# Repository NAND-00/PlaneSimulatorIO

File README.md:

# PlaneSimulatorIO
Plug'n'play I/O board for connecting flight simulator controls to the PC/MAC via USB with extended X-Plane support.

The I/O board is a USB-HID device designed to connect your flight simulator controls to the flight simulator program. It supports up to 32 digital inputs (buttons or switches), two motorized trims with servo indicators, flaps lever with a servo indicator, fuel quadrant, yoke, pedals and a gear switch with three LED indicators.

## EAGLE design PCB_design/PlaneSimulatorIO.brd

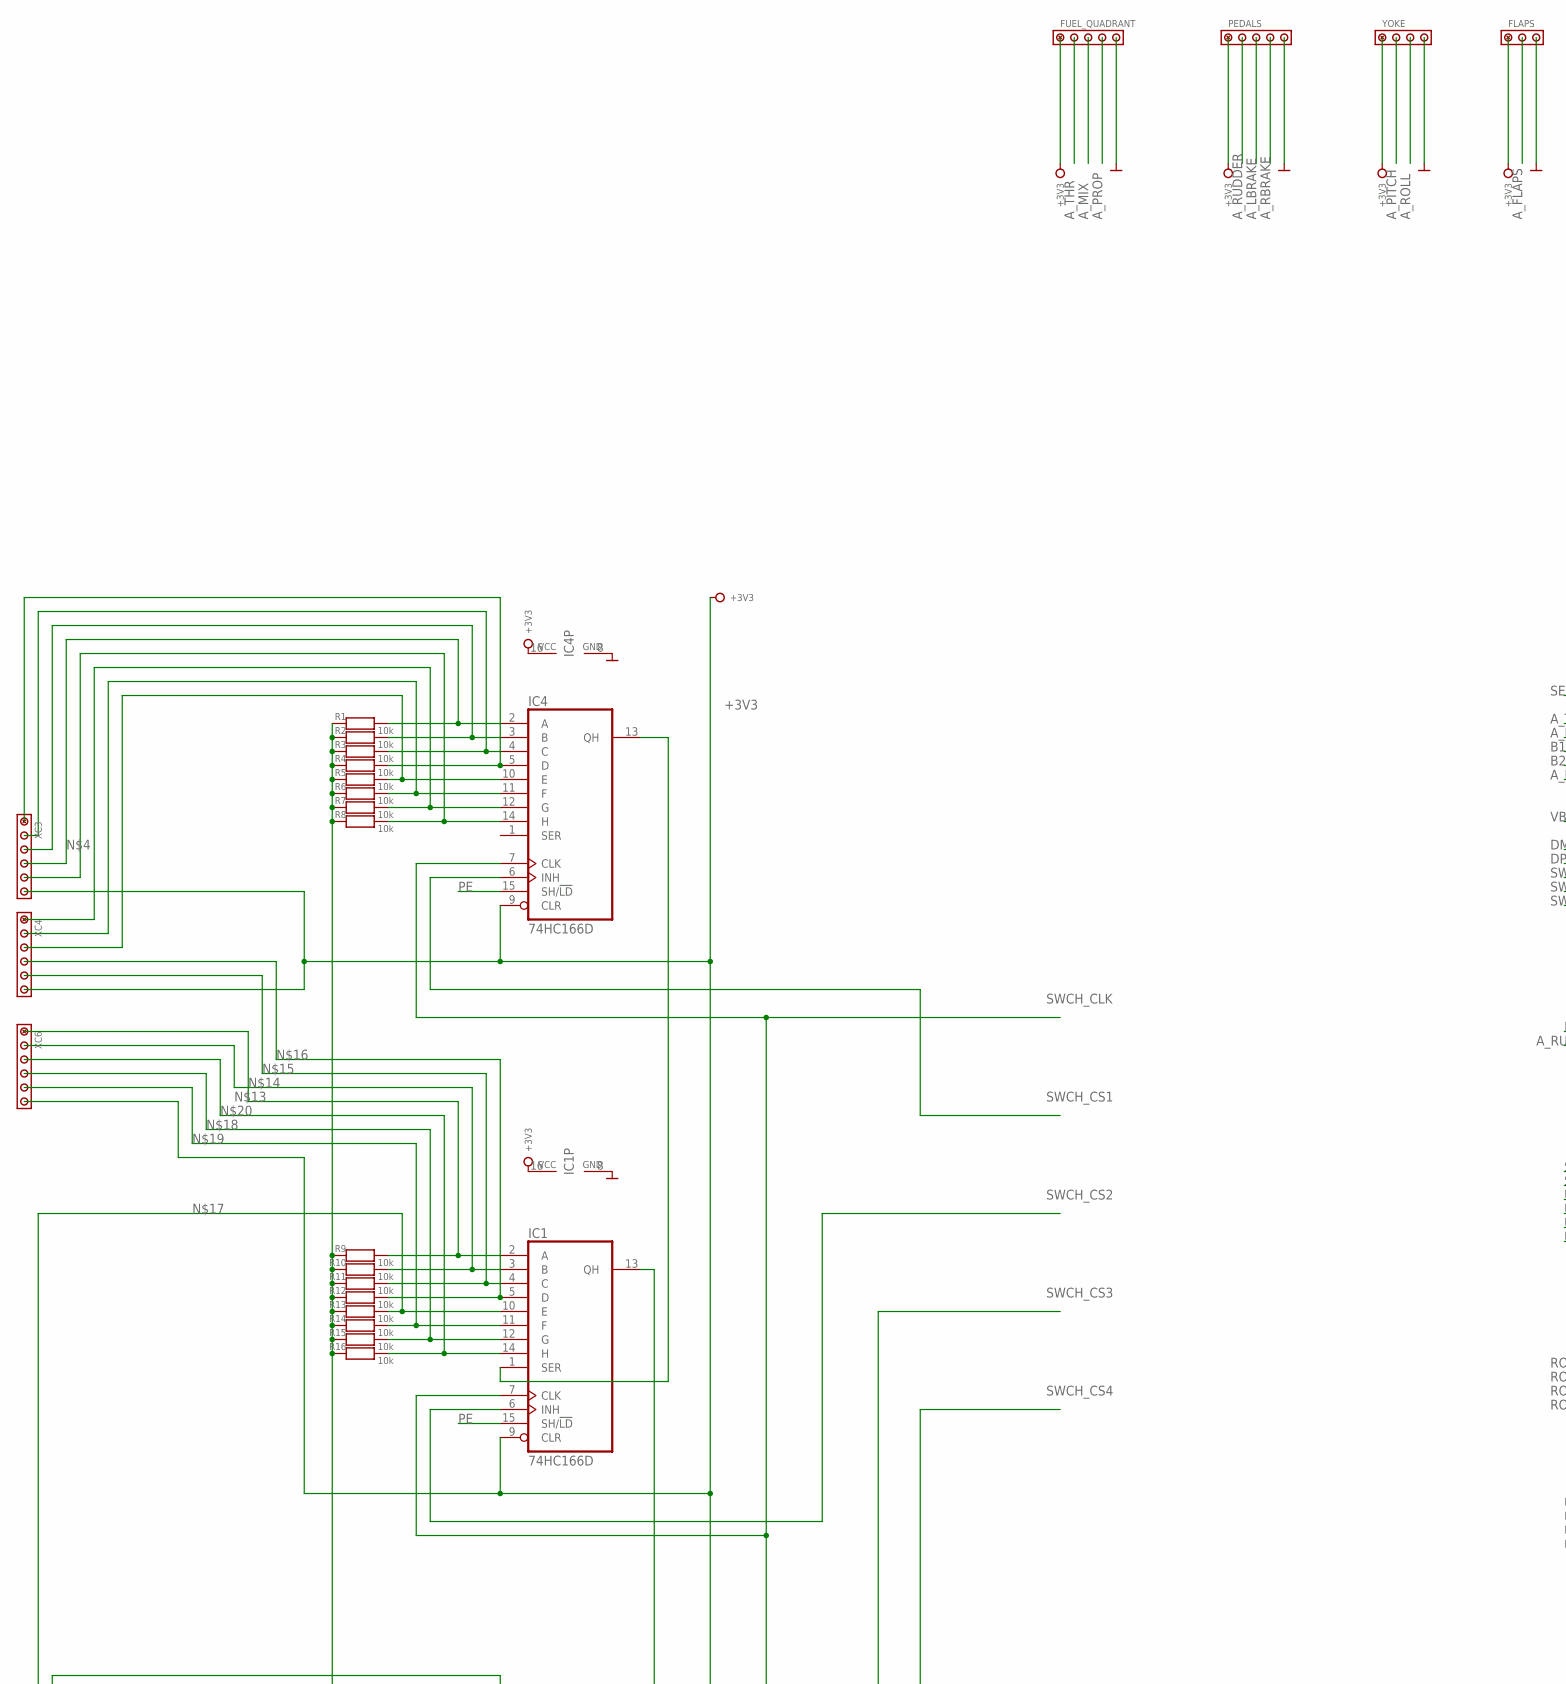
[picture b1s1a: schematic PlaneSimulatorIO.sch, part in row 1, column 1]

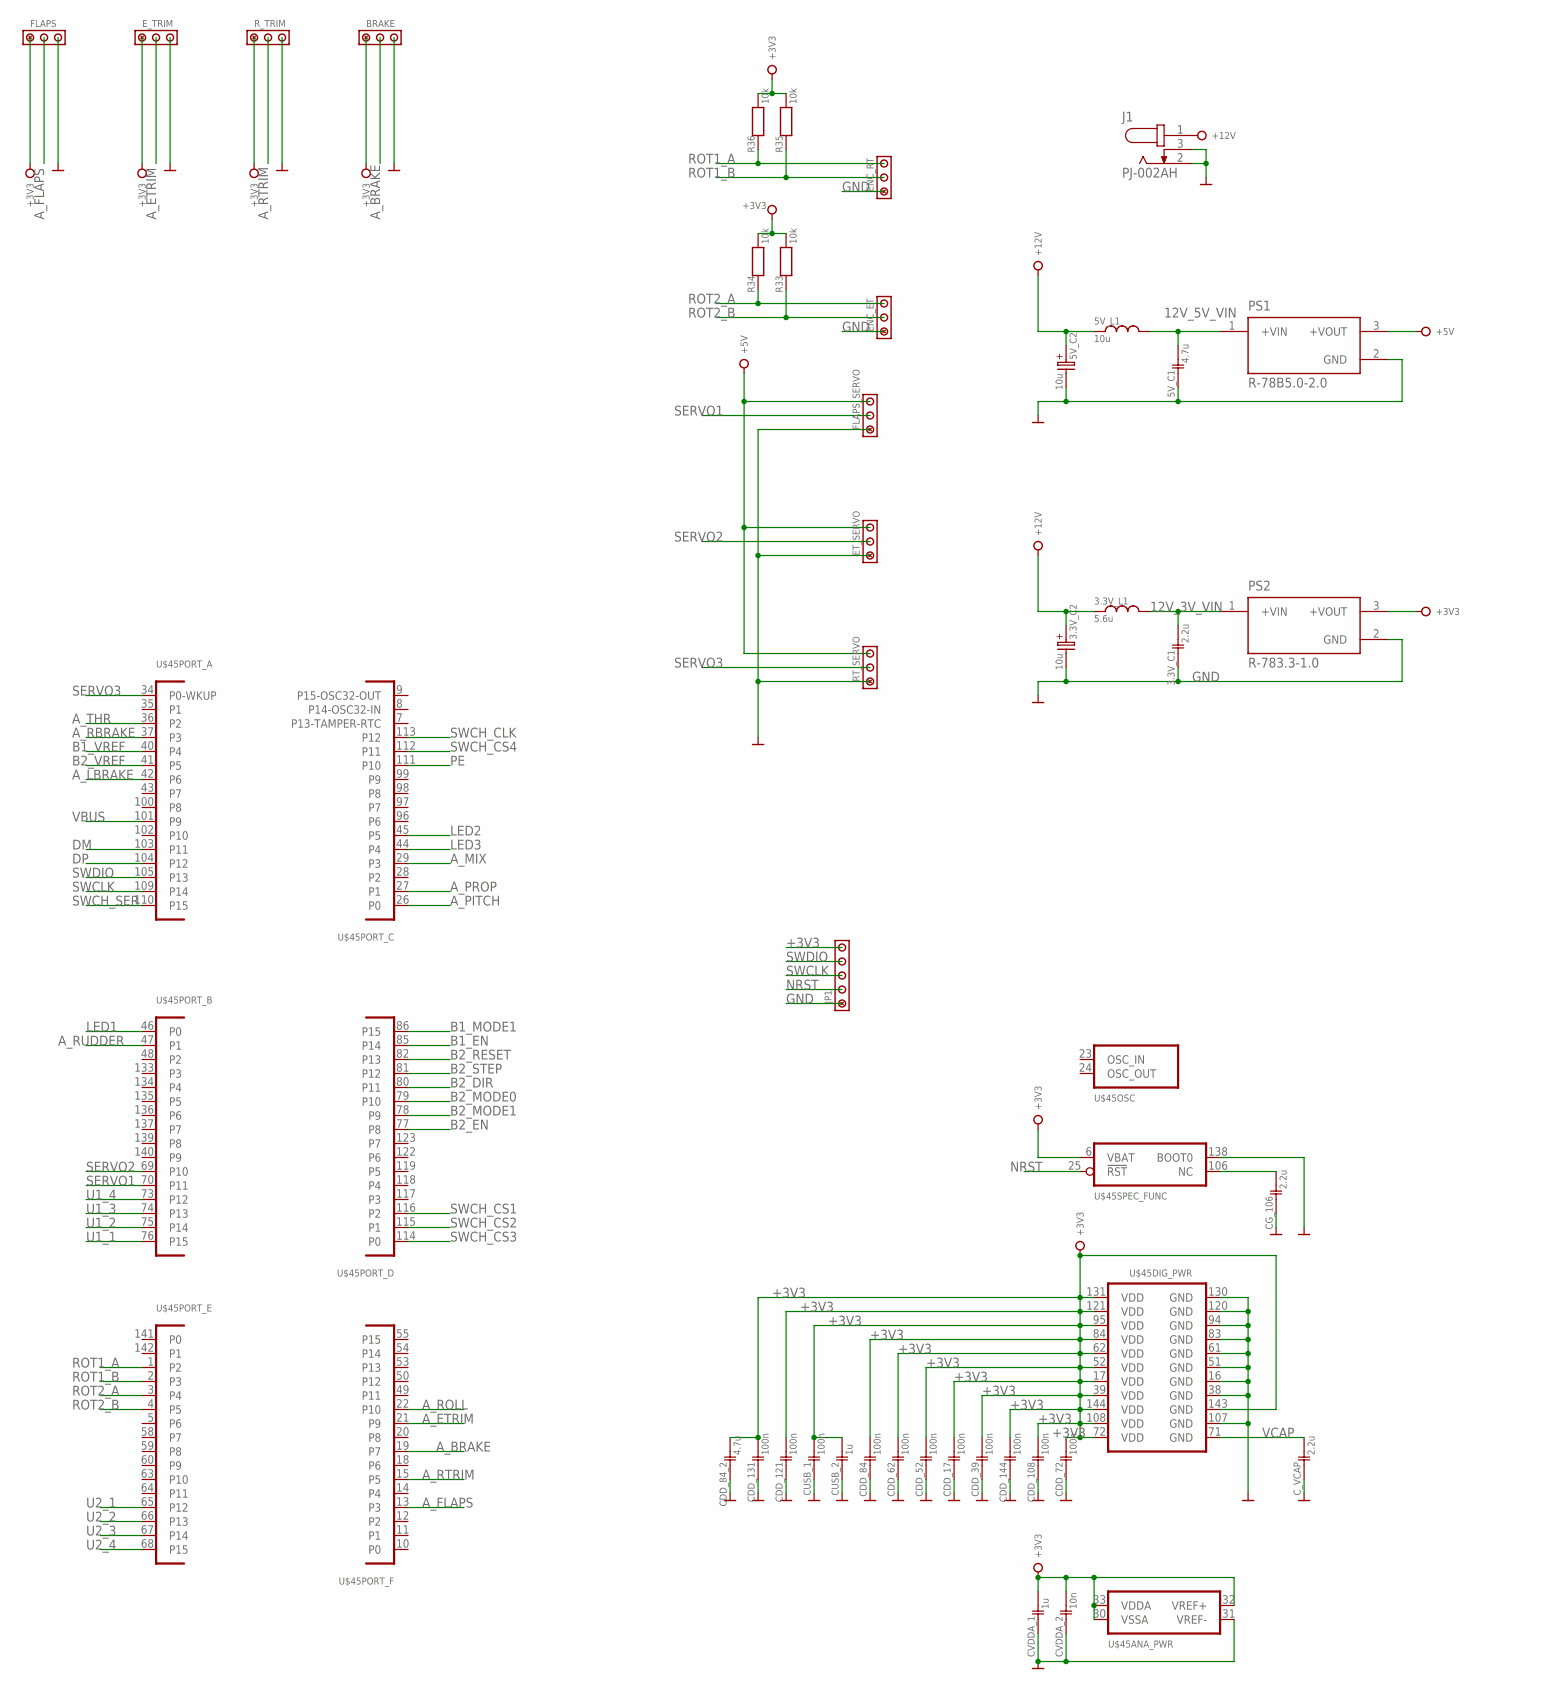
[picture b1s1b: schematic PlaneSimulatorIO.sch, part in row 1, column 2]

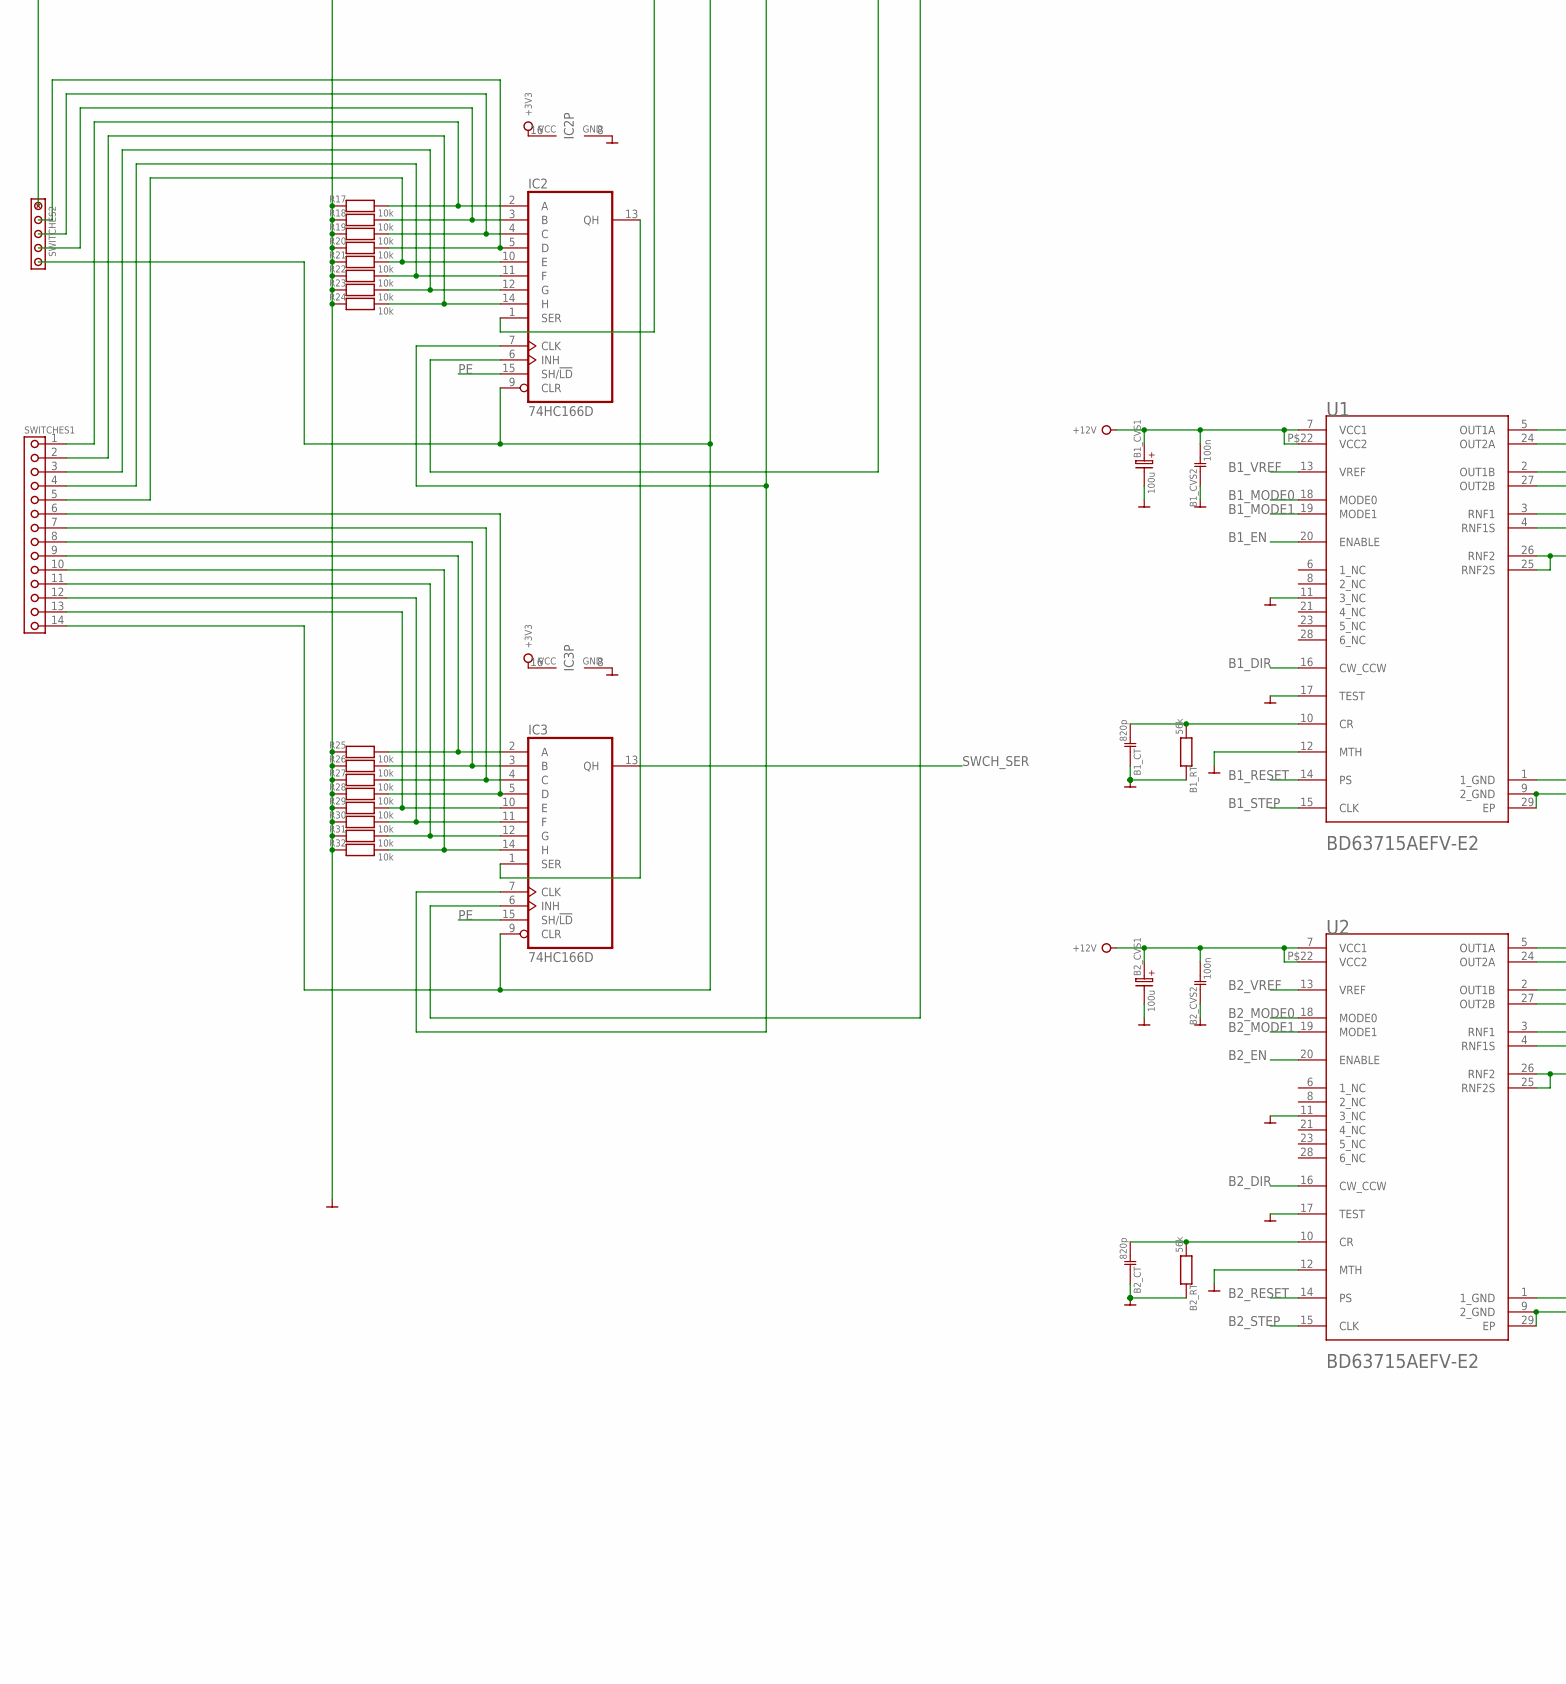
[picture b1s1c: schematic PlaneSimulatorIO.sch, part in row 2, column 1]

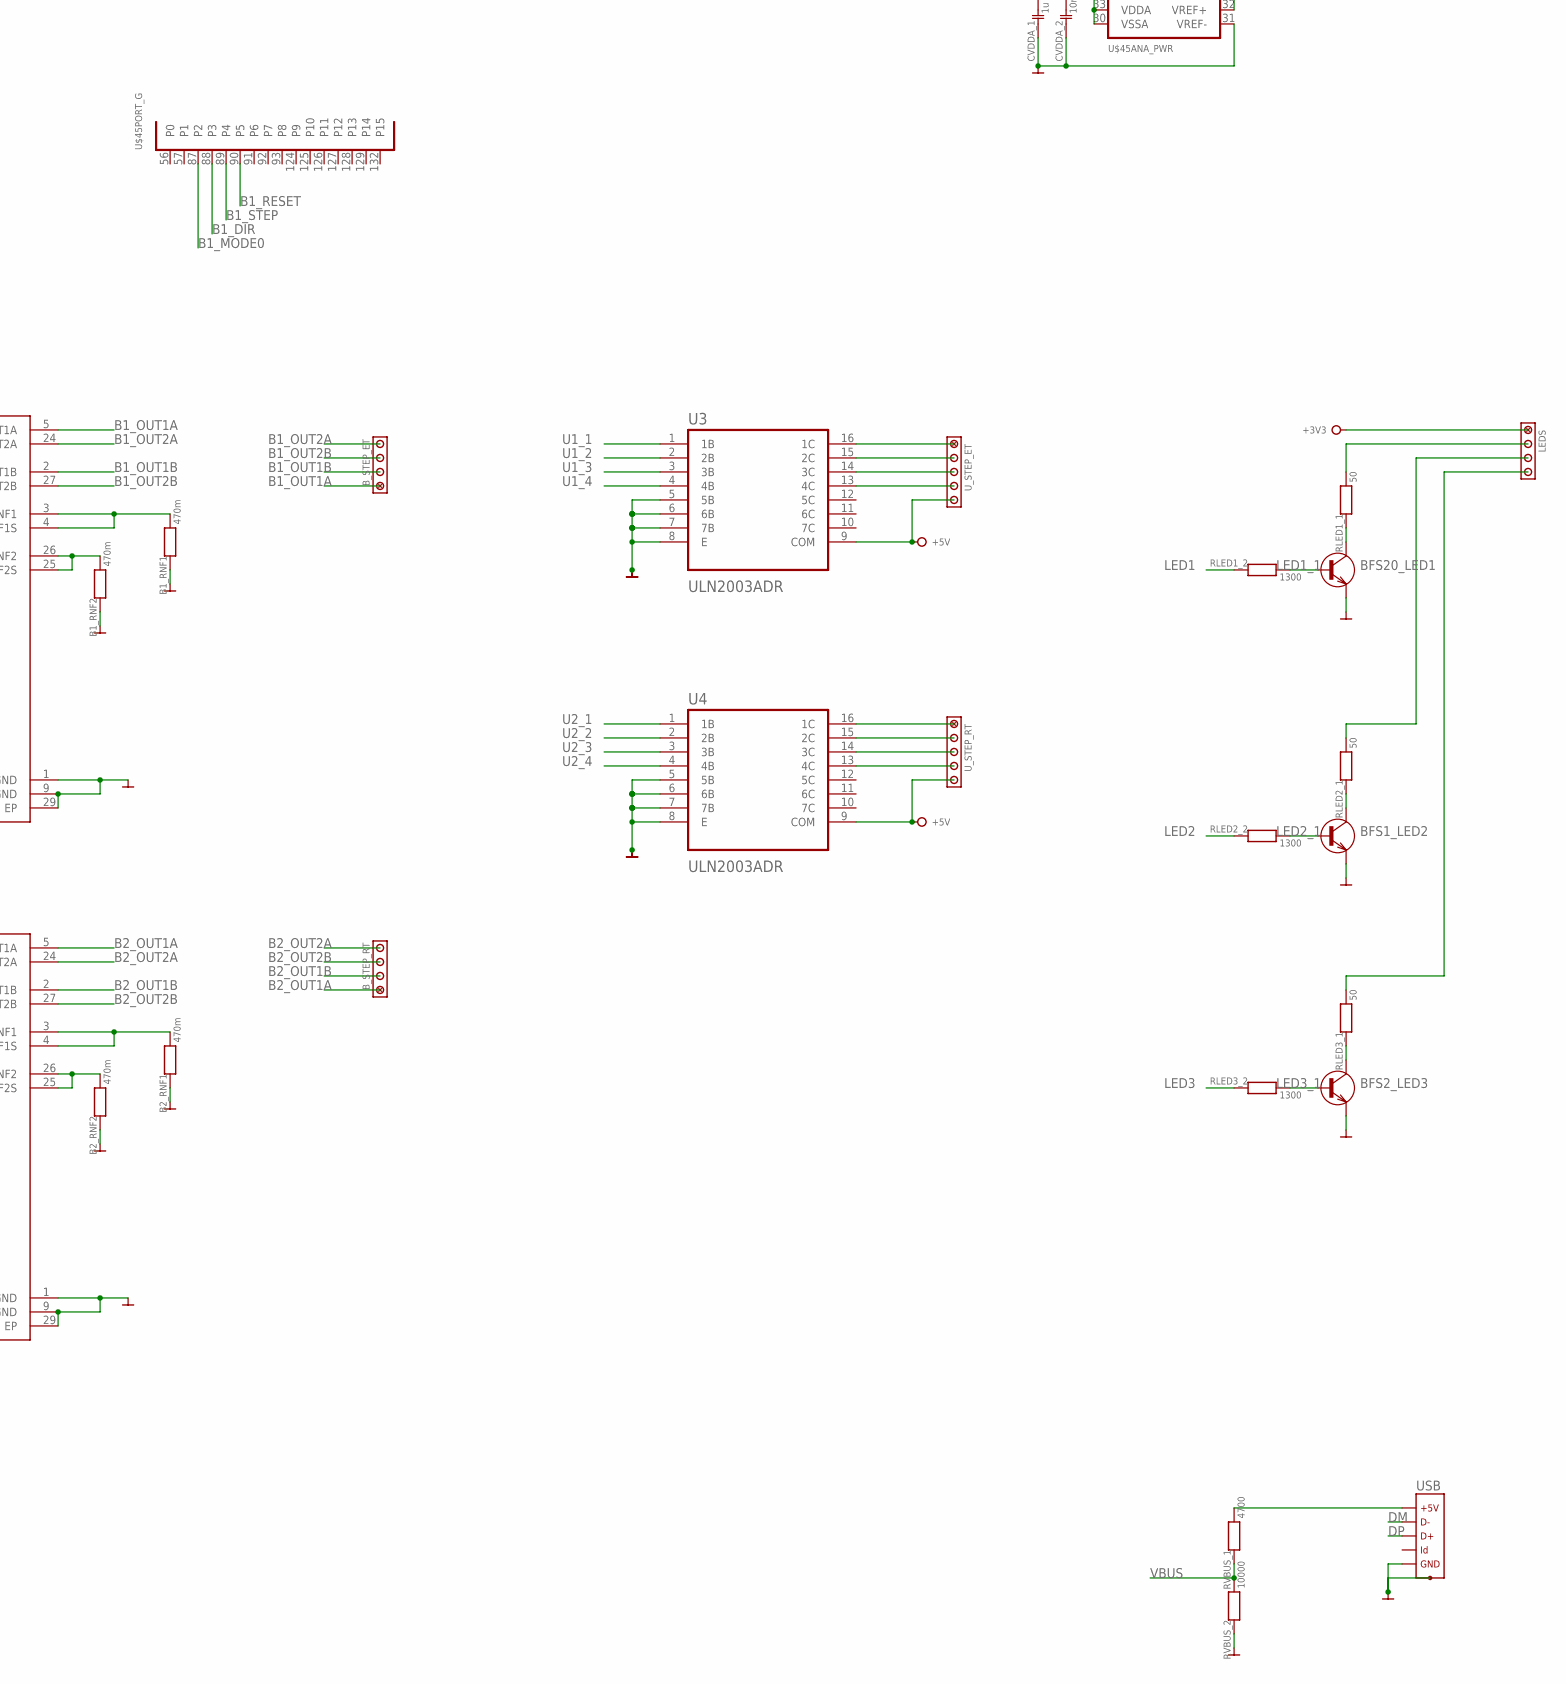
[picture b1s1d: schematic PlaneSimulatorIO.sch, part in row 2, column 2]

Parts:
3.3V_C1: 2.2u; 1206
3.3V_C2, 5V_C2: 10u; EC10-5
3.3V_L1: 5.6u; 0805
5V_C1: 4.7u; 1206
5V_L1: 10u; DR74
B1_CT, B2_CT: 820p; 0603
B1_CVS1, B2_CVS1: 100u; EC10-5
B1_CVS2, B2_CVS2: 100n; 0603
B1_RNF1, B1_RNF2, B2_RNF1, B2_RNF2: 470m; 1206
B1_RT, B2_RT: 56k; 0603
BFS1_LED2, BFS2_LED3, BFS20_LED1: #NPNSOT23-3L; SOT23-3L
BRAKE: MCV/03; MCV3
B_STEP_ET: MCV/04; MCV4
B_STEP_RT: MCV/04; MCV4
CDD_17, CDD_39, CDD_52, CDD_62, CDD_72, CDD_84, CDD_108, CDD_121, CDD_131, CDD_144: 100n; 0603
CDD_84_2: 4.7u; 0603
CG_106: 2.2u; 0603
CUSB_1: 100n; 0603
CUSB_2: 1u; 0603
CVDDA_1: 1u; 0603
CVDDA_2: 10n; 0603
C_VCAP: 2.2u; 0603
ENC_ET: MCV/03; MCV3
ENC_RT: MCV/03; MCV3
ET_SERVO: MCV/03; MCV3
E_TRIM: MCV/03; MCV3
FLAPS: MCV/03; MCV3
FLAPS_SERVO: MCV/03; MCV3
FUEL_QUADRANT: MCV/05; MCV5
IC1, IC2, IC3, IC4: 74HC166D; SO16
J1: PJ-002AH; CUI_PJ-002AH
JP1: JP_05JP_05-2.54; JP_05
LEDS: MCV/04; MCV4
PEDALS: MCV/05; MCV5
PS1: R-78B5.0-2.0; CONV_R-78B5.0-2.0
PS2: R-783.3-1.0; CONV_R-783.3-1.0
R1, R2, R3, R4, R5, R6, R7, R8, R9, R10, R11, R12, R13, R14, R15, R16, R17, R18, R19, R20, R21, R22, R23, R24, R25, R26, R27, R28, R29, R30, R31, R32, R33, R34, R35, R36: 10k; 0603
RLED1_1, RLED2_1, RLED3_1: 50; 0603
RLED1_2, RLED2_2, RLED3_2: 1300; 0603
RT_SERVO: MCV/03; MCV3
RVBUS_1: 4700; 0603
RVBUS_2: 10000; 0603
R_TRIM: MCV/03; MCV3
SWITCHES1: 14MCV3.81; MCV14
SWITCHES2: MCV/05; MCV5
U1, U2: ROHM_BD63715AEFV-E2ROHM_BD63715AEFV-E2_0_3; ROHM_BD63715AEFV-E2_3
U3, U4: ULN2003ADR; SOIC127P600X175-16N
U$45: STM32F103ZE; SQFP-S-20X20-144
USB: USB_5PIN_10118192-0001LF; USB-MICRO-H_10118192-0001LF
U_STEP_ET: MCV/05; MCV5
U_STEP_RT: MCV/05; MCV5
XC3, XC4, XC6: MCV/06; MCV6
YOKE: MCV/04; MCV4

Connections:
12V_3V_VIN: 3.3V_C1.2, 3.3V_L1.2, PS2.1 (+VIN)
12V_5V_VIN: 5V_C1.2, 5V_L1.2, PS1.1 (+VIN)
+3V3: BRAKE.1, CDD_17.2, CDD_39.2, CDD_52.2, CDD_62.2, CDD_72.2, CDD_84.2, CDD_84_2.2, CDD_108.2, CDD_121.2, CDD_131.2, CDD_144.2, CUSB_1.2, CUSB_2.2, CVDDA_1.2, CVDDA_2.2, E_TRIM.1, FLAPS.1, FUEL_QUADRANT.1, IC1.9 (CLR), IC1.16 (VCC), IC2.9 (CLR), IC2.16 (VCC), IC3.9 (CLR), IC3.16 (VCC), IC4.9 (CLR), IC4.16 (VCC), JP1.5, LEDS.1, PEDALS.1, PS2.3 (+VOUT), R33.2, R34.2, R35.2, R36.2, R_TRIM.1, SWITCHES1.14, SWITCHES2.5, U$45.6 (VBAT), U$45.17 (VDD), U$45.30 (VSSA), U$45.32 (VREF+), U$45.33 (VDDA), U$45.39 (VDD), U$45.52 (VDD), U$45.62 (VDD), U$45.72 (VDD), U$45.84 (VDD), U$45.95 (VDD), U$45.108 (VDD), U$45.121 (VDD), U$45.131 (VDD), U$45.143 (GND), U$45.144 (VDD), XC3.6, XC4.6, XC6.6, YOKE.1
+5V: ET_SERVO.3, FLAPS_SERVO.3, PS1.3 (+VOUT), RT_SERVO.3, U3.9 (COM), U4.9 (COM), U_STEP_ET.5, U_STEP_RT.5
+12V: 3.3V_C2.1, 3.3V_L1.1, 5V_C2.1, 5V_L1.1, B1_CVS1.1, B1_CVS2.2, B2_CVS1.1, B2_CVS2.2, J1.1, U1.7 (VCC1), U1.P$22 (VCC2), U2.7 (VCC1), U2.P$22 (VCC2)
A_BRAKE: BRAKE.2, U$45.19 (P7)
A_ETRIM: E_TRIM.2, U$45.21 (P9)
A_FLAPS: FLAPS.2, U$45.13 (P3)
A_LBRAKE: PEDALS.3, U$45.42 (P6)
A_MIX: FUEL_QUADRANT.3, U$45.29 (P3)
A_PITCH: U$45.26 (P0), YOKE.2
A_PROP: FUEL_QUADRANT.4, U$45.27 (P1)
A_RBRAKE: PEDALS.4, U$45.37 (P3)
A_ROLL: U$45.22 (P10), YOKE.3
A_RTRIM: R_TRIM.2, U$45.15 (P5)
A_RUDDER: PEDALS.2, U$45.47 (P1)
A_THR: FUEL_QUADRANT.2, U$45.36 (P2)
B1_DIR: U1.16 (CW_CCW), U$45.88 (P3)
B1_EN: U1.20 (ENABLE), U$45.85 (P14)
B1_MODE0: U1.18 (MODE0), U$45.87 (P2)
B1_MODE1: U1.19 (MODE1), U$45.86 (P15)
B1_OUT1A: B_STEP_ET.1, U1.5 (OUT1A)
B1_OUT1B: B_STEP_ET.2, U1.2 (OUT1B)
B1_OUT2A: B_STEP_ET.4, U1.24 (OUT2A)
B1_OUT2B: B_STEP_ET.3, U1.27 (OUT2B)
B1_RESET: U1.14 (PS), U$45.90 (P5)
B1_STEP: U1.15 (CLK), U$45.89 (P4)
B1_VREF: U1.13 (VREF), U$45.40 (P4)
B2_DIR: U2.16 (CW_CCW), U$45.80 (P11)
B2_EN: U2.20 (ENABLE), U$45.77 (P8)
B2_MODE0: U2.18 (MODE0), U$45.79 (P10)
B2_MODE1: U2.19 (MODE1), U$45.78 (P9)
B2_OUT1A: B_STEP_RT.1, U2.5 (OUT1A)
B2_OUT1B: B_STEP_RT.2, U2.2 (OUT1B)
B2_OUT2A: B_STEP_RT.4, U2.24 (OUT2A)
B2_OUT2B: B_STEP_RT.3, U2.27 (OUT2B)
B2_RESET: U2.14 (PS), U$45.82 (P13)
B2_STEP: U2.15 (CLK), U$45.81 (P12)
B2_VREF: U2.13 (VREF), U$45.41 (P5)
DM: U$45.103 (P11), USB.D- (2)
DP: U$45.104 (P12), USB.D+ (3)
GND: 3.3V_C1.1, 3.3V_C2.2, 5V_C1.1, 5V_C2.2, B1_CT.1, B1_CVS1.2, B1_CVS2.1, B1_RNF1.1, B1_RNF2.1, B1_RT.1, B2_CT.1, B2_CVS1.2, B2_CVS2.1, B2_RNF1.1, B2_RNF2.1, B2_RT.1, BFS1_LED2.2 (E), BFS2_LED3.2 (E), BFS20_LED1.2 (E), BRAKE.3, CDD_17.1, CDD_39.1, CDD_52.1, CDD_62.1, CDD_72.1, CDD_84.1, CDD_84_2.1, CDD_108.1, CDD_121.1, CDD_131.1, CDD_144.1, CG_106.1, CUSB_1.1, CUSB_2.1, CVDDA_1.1, CVDDA_2.1, C_VCAP.1, ENC_ET.1, ENC_RT.1, ET_SERVO.1, E_TRIM.3, FLAPS.3, FLAPS_SERVO.1, FUEL_QUADRANT.5, IC1.8 (GND), IC2.8 (GND), IC3.8 (GND), IC4.8 (GND), J1.2, J1.3, JP1.1, PEDALS.5, PS1.2 (GND), PS2.2 (GND), R1.1, R2.1, R3.1, R4.1, R5.1, R6.1, R7.1, R8.1, R9.1, R10.1, R11.1, R12.1, R13.1, R14.1, R15.1, R16.1, R17.1, R18.1, R19.1, R20.1, R21.1, R22.1, R23.1, R24.1, R25.1, R26.1, R27.1, R28.1, R29.1, R30.1, R31.1, R32.1, RT_SERVO.1, RVBUS_2.1, R_TRIM.3, U1.1 (1_GND), U1.9 (2_GND), U1.11 (3_NC), U1.12 (MTH), U1.17 (TEST), U1.29 (EP), U2.1 (1_GND), U2.9 (2_GND), U2.11 (3_NC), U2.12 (MTH), U2.17 (TEST), U2.29 (EP), U3.5 (5B), U3.6 (6B), U3.7 (7B), U3.8 (E), U4.5 (5B), U4.6 (6B), U4.7 (7B), U4.8 (E), U$45.16 (GND), U$45.31 (VREF-), U$45.38 (GND), U$45.51 (GND), U$45.61 (GND), U$45.83 (GND), U$45.94 (GND), U$45.107 (GND), U$45.120 (GND), U$45.130 (GND), U$45.138 (BOOT0), USB.GND (5), USB.S1 (S), USB.S2 (S), YOKE.4
LED1: RLED1_2.1, U$45.46 (P0)
LED1_1: BFS20_LED1.1 (B), RLED1_2.2
LED2: RLED2_2.1, U$45.45 (P5)
LED2_1: BFS1_LED2.1 (B), RLED2_2.2
LED3: RLED3_2.1, U$45.44 (P4)
LED3_1: BFS2_LED3.1 (B), RLED3_2.2
unnamed: IC4.5 (D), R4.2, XC3.1
unnamed: IC4.4 (C), R3.2, XC3.2
unnamed: IC4.3 (B), R2.2, XC3.3
unnamed: IC4.2 (A), R1.2, XC3.4
unnamed: IC4.10 (E), R5.2, XC4.3
unnamed: IC4.11 (F), R6.2, XC4.2
unnamed: IC4.12 (G), R7.2, XC4.1
unnamed: IC4.14 (H), R8.2, XC3.5
unnamed: U4.16 (1C), U_STEP_RT.1
unnamed: U4.13 (4C), U_STEP_RT.4
unnamed: U4.14 (3C), U_STEP_RT.3
unnamed: IC1.2 (A), R9.2, XC6.1
unnamed: IC1.3 (B), R10.2, XC6.2
unnamed: IC1.4 (C), R11.2, XC4.5
unnamed: IC1.5 (D), R12.2, XC4.4
unnamed: IC1.10 (E), R13.2, SWITCHES2.1
unnamed: IC1.11 (F), R14.2, XC6.5
unnamed: IC1.12 (G), R15.2, XC6.4
unnamed: IC1.14 (H), R16.2, XC6.3
unnamed: U4.15 (2C), U_STEP_RT.2
unnamed: U3.16 (1C), U_STEP_ET.1
unnamed: U3.15 (2C), U_STEP_ET.2
unnamed: IC2.3 (B), R18.2, SWITCHES2.4
unnamed: IC2.4 (C), R19.2, SWITCHES2.3
unnamed: IC2.5 (D), R20.2, SWITCHES2.2
unnamed: IC2.2 (A), R17.2, SWITCHES1.1
unnamed: IC2.14 (H), R24.2, SWITCHES1.2
unnamed: IC2.12 (G), R23.2, SWITCHES1.3
unnamed: IC2.11 (F), R22.2, SWITCHES1.4
unnamed: IC2.10 (E), R21.2, SWITCHES1.5
unnamed: U3.14 (3C), U_STEP_ET.3
unnamed: U3.13 (4C), U_STEP_ET.4
unnamed: B2_CT.2, B2_RT.2, U2.10 (CR)
unnamed: B2_RNF1.2, U2.3 (RNF1), U2.4 (RNF1S)
unnamed: IC3.5 (D), R28.2, SWITCHES1.6
unnamed: IC3.4 (C), R27.2, SWITCHES1.7
unnamed: IC3.3 (B), R26.2, SWITCHES1.8
unnamed: IC3.2 (A), R25.2, SWITCHES1.9
unnamed: IC3.14 (H), R32.2, SWITCHES1.10
unnamed: IC3.12 (G), R31.2, SWITCHES1.11
unnamed: IC3.11 (F), R30.2, SWITCHES1.12
unnamed: B2_RNF2.2, U2.25 (RNF2S), U2.26 (RNF2)
unnamed: IC3.10 (E), R29.2, SWITCHES1.13
unnamed: CG_106.2, U$45.106 (NC)
unnamed: BFS1_LED2.3 (C), RLED2_1.1
unnamed: IC2.13 (QH), IC3.1 (SER)
unnamed: IC1.13 (QH), IC2.1 (SER)
unnamed: IC1.1 (SER), IC4.13 (QH)
unnamed: B1_RNF1.2, U1.3 (RNF1), U1.4 (RNF1S)
unnamed: B1_CT.2, B1_RT.2, U1.10 (CR)
unnamed: B1_RNF2.2, U1.25 (RNF2S), U1.26 (RNF2)
unnamed: RVBUS_1.2, USB.VBUS (1)
unnamed: BFS20_LED1.3 (C), RLED1_1.1
unnamed: LEDS.2, RLED1_1.2
unnamed: LEDS.3, RLED2_1.2
unnamed: BFS2_LED3.3 (C), RLED3_1.1
unnamed: LEDS.4, RLED3_1.2
NRST: JP1.2, U$45.25 (!RST)
PE: IC1.15 (SH/!LD), IC2.15 (SH/!LD), IC3.15 (SH/!LD), IC4.15 (SH/!LD), U$45.111 (P10)
ROT1_A: ENC_RT.3, R36.1, U$45.1 (P2)
ROT1_B: ENC_RT.2, R35.1, U$45.2 (P3)
ROT2_A: ENC_ET.3, R34.1, U$45.3 (P4)
ROT2_B: ENC_ET.2, R33.1, U$45.4 (P5)
SERVO1: FLAPS_SERVO.2, U$45.70 (P11)
SERVO2: ET_SERVO.2, U$45.69 (P10)
SERVO3: RT_SERVO.2, U$45.34 (P0-WKUP)
SWCH_CLK: IC1.7 (CLK), IC2.7 (CLK), IC3.7 (CLK), IC4.7 (CLK), U$45.113 (P12)
SWCH_CS1: IC4.6 (INH), U$45.116 (P2)
SWCH_CS2: IC1.6 (INH), U$45.115 (P1)
SWCH_CS3: IC2.6 (INH), U$45.114 (P0)
SWCH_CS4: IC3.6 (INH), U$45.112 (P11)
SWCH_SER: IC3.13 (QH), U$45.110 (P15)
SWCLK: JP1.3, U$45.109 (P14)
SWDIO: JP1.4, U$45.105 (P13)
U1_1: U3.1 (1B), U$45.76 (P15)
U1_2: U3.2 (2B), U$45.75 (P14)
U1_3: U3.3 (3B), U$45.74 (P13)
U1_4: U3.4 (4B), U$45.73 (P12)
U2_1: U4.1 (1B), U$45.65 (P12)
U2_2: U4.2 (2B), U$45.66 (P13)
U2_3: U4.3 (3B), U$45.67 (P14)
U2_4: U4.4 (4B), U$45.68 (P15)
VBUS: RVBUS_1.1, RVBUS_2.2, U$45.101 (P9)
VCAP: C_VCAP.2, U$45.71 (GND)

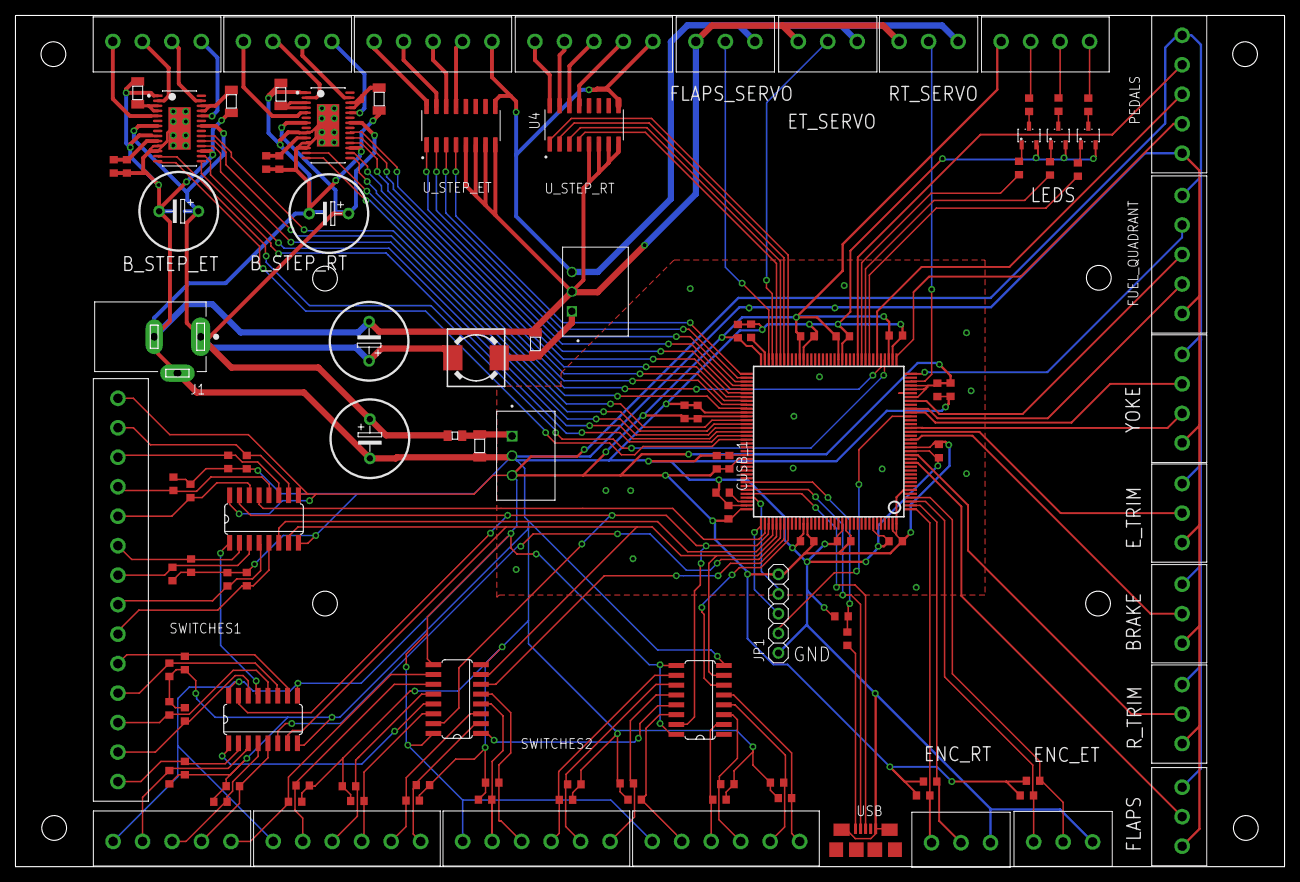
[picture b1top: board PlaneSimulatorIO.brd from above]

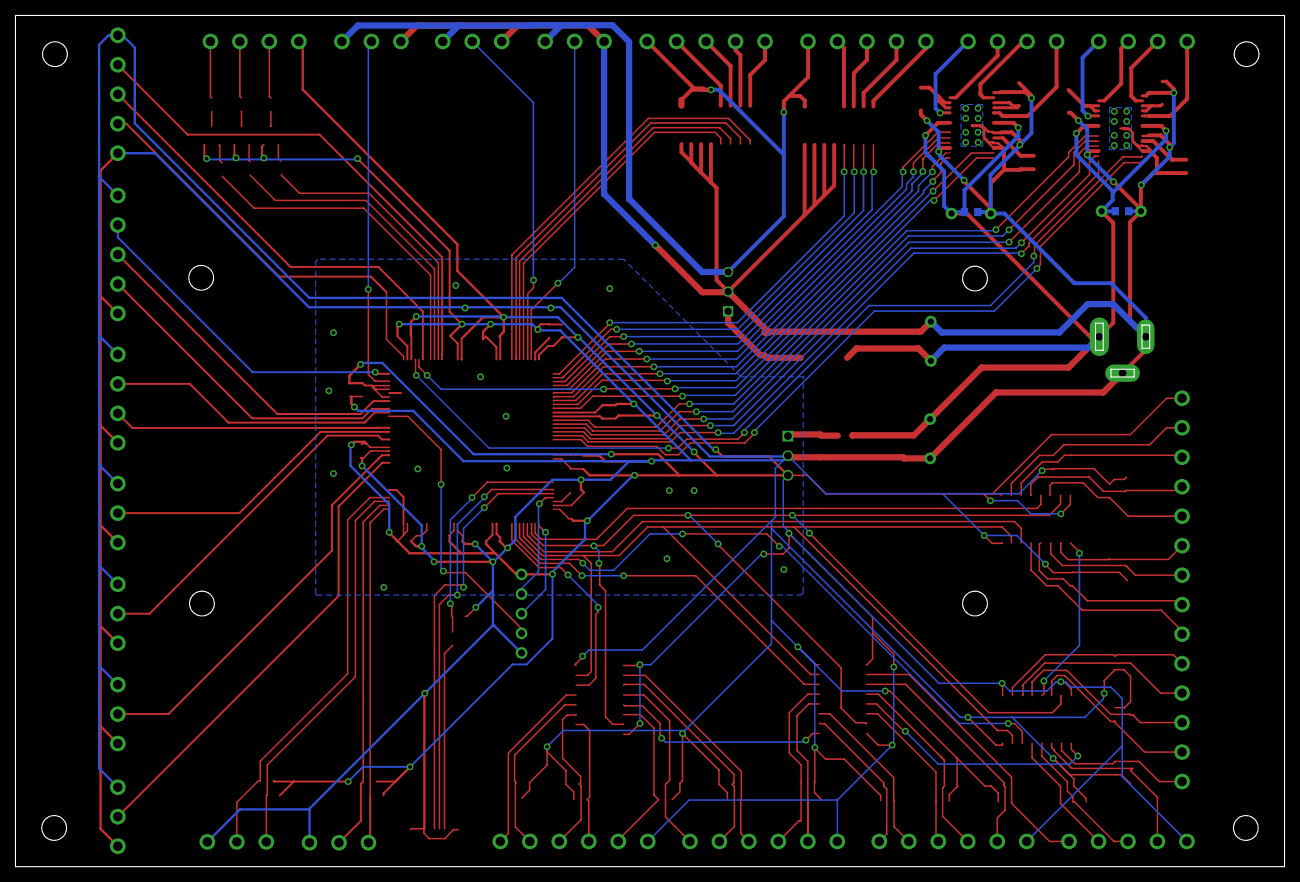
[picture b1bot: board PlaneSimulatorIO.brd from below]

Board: 2 copper layers, 164.0 x 110.0 mm, 126 parts (2 on the bottom side), 132 nets.

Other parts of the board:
U$1, U$2, U$3, U$4, U$5, U$43, U$44, U$62: M3-HOLE

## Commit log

2023-01-29 initial project upload
2023-01-29 added PCB design
2023-08-16 Changed autopilot dataref
2023-08-17 Compiled plugin
2023-08-17 Split main program into multiple files
